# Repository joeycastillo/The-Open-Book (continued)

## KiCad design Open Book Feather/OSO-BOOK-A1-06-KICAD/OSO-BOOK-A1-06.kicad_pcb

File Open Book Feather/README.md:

# Notes on the Open Book PCB files

The current working, tested revision is **Open Book A1 Rev 06** (**OSO-BOOK-A1-06**). For the sake of clarity, I've removed revisions 01 through 04; if you made one of these old boards, these notes remain.

## Open Book A1 Rev 01 Errata

I imagine you don't have this board; it was the first test, and was replaced with revision 2 almost immediately. It had a couple of big issues:

* The buttons on the shift register floated, because there were no pull-up resistors. This rendered the buttons unusable.
* The Neopixel, in addition to being in a really inconvenient place, was powered by VHI instead of the 3V regulator, which made it power up before everything else and shine bright blue until you took control of it. It also wouldn't turn off when the enable switch was thrown.

## Open Book A1 Rev 02 Errata

There are two errors on this revision's descriptive silkscreen: first, at the bottom, in the "Button Register" block, the shift register's pins are listed as:

    Pins: 
    BUTTON_LATCH: D48/PB31
    BUTTON_OUT:  D49/PB30
    BUTTON_CLOCK: D50/PB00

The correct mapping is:

    Pins: 
    BUTTON_LATCH: D50/PB00
    BUTTON_OUT:  D49/PB30
    BUTTON_CLOCK: D48/PB31

Second, the SAM D51 Microcontroller block erroneously lists the UART's SERCOM as SERCOM0. It is in fact SERCOM5.

## Open Book A1 Rev 03

Revision 3 was never fabricated; it simply fixed the first error above, but was otherwise identical to Revision 2. I wanted to correct the error in case anyone was building along at home, and bumped the revision to make it clear which version had the issue. It still has the incorrect SERCOM listed, though; that was not caught until later.

Note that the pin muxing changed after revision 3; if you have board revision A1-01, A1-02 or A1-03, you will need to set a flag when compiling your code. In the Arduino IDE, this setting is in `Tools -> Hardware Revision`. In CircuitPython, you can just use the digital pin numbers as labeled on your silkscreen to access the correct pins.

## Open Book A1 Rev 04

This board has the final pinout (no need to set the Hardware Revision flag), and adds several features:

* Microphone shutdown pin
* USB voltage monitor (detect when plugged in to external power)
* Battery full indicator

This is the last revision with the SERCOM0/SERCOM5 silkscreen error.

## Open Book A1 Rev 05

This is identical to Rev 04, but fixes the silkscreen error in the SAM D51 block. It also adds a RC filter to the USB cable shield (recommendation from the SAM D51 data sheet), and tweaks the through-hole button footprints for a slightly better fit.

This version works quite well. If you have this version, there is no need to get the A1-06 version.

## Open Book A1 Rev 06

This is the final version of the A1-type hardware. It adds pull-up resistors for the Babel Flash chip and MicroSD card, and bias resistors for the audio output on the headphone jack.

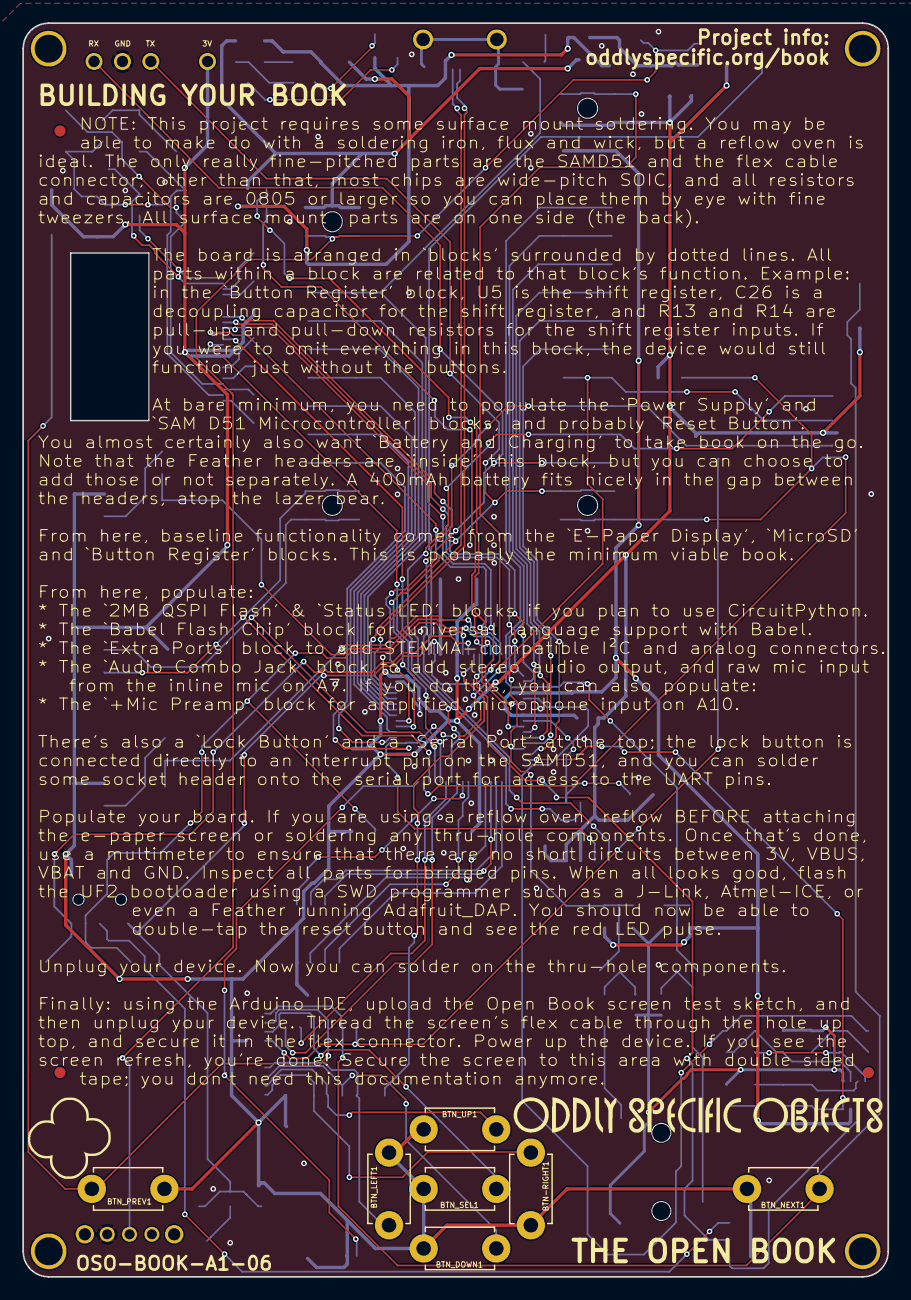
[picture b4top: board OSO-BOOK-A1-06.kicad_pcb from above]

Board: 2 copper layers, 77.5 x 112.3 mm, 136 parts (0 on the bottom side), 100 nets.

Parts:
BTN-RIGHT1: SWITCH_PUSHBUTTONEVQ-PE; TACT_PANA-EVQ
BTN_DOWN1: SWITCH_PUSHBUTTONEVQ-PE; TACT_PANA-EVQ
BTN_LEFT1: SWITCH_PUSHBUTTONEVQ-PE; TACT_PANA-EVQ
BTN_LOCK1: SPST_TACTILE_SWITCHRA; TL3330AF130QG
BTN_NEXT1: SWITCH_PUSHBUTTONEVQ-PE; TACT_PANA-EVQ
BTN_PREV1: SWITCH_PUSHBUTTONEVQ-PE; TACT_PANA-EVQ
BTN_RESET1: SPST_TACTILE_SWITCHRA; TL3330AF130QG
BTN_SEL1: SWITCH_PUSHBUTTONEVQ-PE; TACT_PANA-EVQ
BTN_UP1: SWITCH_PUSHBUTTONEVQ-PE; TACT_PANA-EVQ
C1, C2, C4, C11: 10µF; 0805-NO
C3, C9, C12, C14, C15, C16, C17, C29: 1uF; 0805-NO
C5, C7, C25: 10uF; 0805_10MGAP
C6, C8, C10, C26, C28: 1uF; 0805_10MGAP
C13: 0.1uF; 0805_10MGAP
C18, C19, C20, C21, C22, C23: 1uF/25V; 0805-NO
C24: 4.7uF/25V; 0805-NO
C27, C35: 10uF; 0805-NO
C30, C31: 100uF; C1210
C32: 0.1µF; 0805-NO
C33: 0.01uF; 0805-NO
C34: 100pF; 0805-NO
C36: 4.5nF; 0805-NO
CHG1: AMBER; CHIP-LED0805
D1: MBR120; SOD-123
D2, D3, D4: MBR0530; SOD-123
D5, D6: 3.6V; SOD-123
DNP_NEXT_ALT1: SPST_TACTILE_SWITCHRA; TL3330AF130QG
DNP_PREV_ALT1: SPST_TACTILE_SWITCHRA; TL3330AF130QG
FB1, FB2: Ferrite; 0805
FID1, FID2, FID3, FID4, FID5, FID6: FIDUCIAL_1MM
FUL1: GREEN; CHIP-LED0805
GOLD_ORB_SM1: OSHWLOGOLOGO5MM; OSHW_5MM
J1: SJ-43514-SMT; CUI_SJ-43514-SMT
J2: 10118193-0001LF; FCI_10118193-0001LF
JP1: PINHD-1X3; 1X03
JP2: PINHD-1X1; 1X01
L1: 10uH; MICROBUILDER_INDUCTOR_4X4MM_NR401_BIGPADS
LED1: RED; CHIP-LED0805
MICROSD1: MICROSD
MS1: FEATHERWING_SMTDUAL; FEATHERWING_SMT2
NEOPIX1: WS2812B_4020
PORT_A8, PORT_A9: JST PH 3; JSTPH3
PORT_I2C1: JST PH 4; JSTPH4
Q1: DMG341; SOT23-R
Q2: IRLML0100; SOT23-3
R1, R3: 10K; 0805-NO
R2, R11, R26: 100K; 0805-NO
R4, R5, R10, R21, R22, R25: 1K; 0805-NO
R6, R13, R14: 100K; EXBV8V
R7, R8, R28, R29: 10K; 0805_10MGAP
R9: 100; 0805_10MGAP
R12: 0.47ohm; 0805_10MGAP
R15, R16: 1K; _0805MP
R17, R18, R19, R20: 100; 0805-NO
R23, R24, R27: 1M; 0805-NO
R30, R31, R32, R33: 10K; _0805MP
SJ1: SOLDERJUMPER_FIVEWAY
SW1: SPDT_SWITCH; A10767
TP1, TP2, TP6, TP7, TP8: TESTPOINTROUND2MMNO; TESTPOINT_ROUND_2MM_NO
U1: AP2112-3.3; SOT23-5
U2: MCP73831T-2ACI/OT; SOT23-5
U3: ATSAMD51J64-TQFP(10X10); TQFP64-10X10
U4: GD25Q16C; SOIC8_150MIL
U5: 74AC165D; SO16
U6: GD25Q16C; MICROBUILDER_SOIC8_150MIL
U7: MAX4468EKAT; SOT65P280X145-8N
U$1, U$4, U$5, U$7: MOUNTINGHOLE2.5; MOUNTINGHOLE_2.5_PLATED
U$2: WAVESHARE_4_2_INCH_EINK_DISPLAY; EINK_DISPLAY_4_2IN
U$45: OSO_WORDMARK_125X1300MIL_1000DPI
U$47: OSO_BEAR_525X750MIL_1000DPI
U$48: OSO-LOGO-250MIL
U$49: OSO_WORDMARK_THREELINE_450MIL_1000DPI
X1: JSTPH; JSTPH2
X2: 2x5 0.05" SWD; 2X05_1.27MM_BOX_POSTS

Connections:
+3V3: BTN-RIGHT1.P$2, BTN_DOWN1.P$2, BTN_LEFT1.P$2, BTN_NEXT1.P$2, BTN_PREV1.P$2, BTN_SEL1.P$2, BTN_UP1.P$2, C2.1, C3.1, C5.1, C6.1, C9.1, C10.1, C14.1, C17.2, C25.1, C26.1, C27.1, C28.1, C29.1, DNP_NEXT_ALT1.P$2, DNP_PREV_ALT1.P$2, FB1.1, JP2.1, L1.P$1, MICROSD1.4, MS1.2, MS1.2', NEOPIX1.2, PORT_A8.2, PORT_A9.2, PORT_I2C1.2, R7.1, R8.1, R11.1, R13.5, R28.1, R29.1, SJ1.3, TP2.P$1, U1.5, U3.21, U3.34, U3.48, U3.56, U4.8, U5.16, U6.3, U6.7, U6.8, U$2.15, U$2.16, X2.1
/OSO-BOOK-A1-06_1/A2: MS1.7, MS1.7', U3.11
/OSO-BOOK-A1-06_1/A3: MS1.8, MS1.8', U3.12
/OSO-BOOK-A1-06_1/A4: MS1.9, MS1.9', U3.13
/OSO-BOOK-A1-06_1/A5: MS1.10, MS1.10', U3.15
/OSO-BOOK-A1-06_1/A6_BATMON: R6.1, R6.2, U3.62
/OSO-BOOK-A1-06_1/A11_BUSMON: R6.3, R6.4, U3.61
/OSO-BOOK-A1-06_1/D5: MS1.19, MS1.19', U3.35
/OSO-BOOK-A1-06_1/D6: MS1.20, MS1.20', U3.37
/OSO-BOOK-A1-06_1/D9: MS1.21, MS1.21', U3.38
/OSO-BOOK-A1-06_1/D10: MS1.22, MS1.22', U3.41
/OSO-BOOK-A1-06_1/D11: MS1.23, MS1.23', U3.42
/OSO-BOOK-A1-06_1/D12: MS1.24, MS1.24', U3.43
/OSO-BOOK-A1-06_1/SWCLK: R7.2, TP6.P$1, U3.57, X2.4
/OSO-BOOK-A1-06_1/SWDIO: TP7.P$1, U3.58, X2.2
/OSO-BOOK-A1-06_1/USB_N: J2.2, U3.45
/OSO-BOOK-A1-06_1/USB_P: J2.3, U3.46
/OSO-BOOK-A1-06_1/~RESET: C13.2, MS1.1, MS1.1', R8.2, R9.2, TP8.P$1, U3.52, X2.10
/OSO-BOOK-A1-06_2/BUTTON0: BTN_LEFT1.P$1, R14.1, U5.11
/OSO-BOOK-A1-06_2/BUTTON1: BTN_DOWN1.P$1, R14.2, U5.12
/OSO-BOOK-A1-06_2/BUTTON2: BTN_UP1.P$1, R14.3, U5.13
/OSO-BOOK-A1-06_2/BUTTON3: BTN-RIGHT1.P$1, R14.4, U5.14
/OSO-BOOK-A1-06_2/BUTTON4: BTN_SEL1.P$1, R13.3, U5.3
/OSO-BOOK-A1-06_2/BUTTON5: BTN_PREV1.P$1, DNP_PREV_ALT1.P$1, R13.2, U5.4
/OSO-BOOK-A1-06_2/BUTTON6: BTN_NEXT1.P$1, DNP_NEXT_ALT1.P$1, R13.1, U5.5
/OSO-BOOK-A1-06_2/BUTTON7: MICROSD1.CD2, R13.4, U5.6
/OSO-BOOK-A1-06_2/GDR: Q2.1, U$2.2
/OSO-BOOK-A1-06_2/PREVGH: C23.1, D4.C, U$2.21
/OSO-BOOK-A1-06_2/PREVGL: C22.1, D3.A, U$2.23
/OSO-BOOK-A1-06_2/RESE: Q2.2, R12.1, U$2.3
/OSO-BOOK-A1-06_2/VCOM: C21.2, U$2.24
/OSO-BOOK-A1-06_2/VDD: C18.2, U$2.18
/OSO-BOOK-A1-06_2/VGH: C16.2, U$2.5
/OSO-BOOK-A1-06_2/VGL: C15.2, U$2.4
/OSO-BOOK-A1-06_2/VSH: C19.2, U$2.20
/OSO-BOOK-A1-06_2/VSL: C20.2, U$2.22
/OSO-BOOK-A1-06_3/MICAMP_SHDN: SJ1.2, U7.6
/OSO-BOOK-A1-06_3/MIC_BIAS_PWR: R22.2, R24.2, U7.4
A0: MS1.5, MS1.5', R17.2, R30.2, R31.1, U3.3
A1: MS1.6, MS1.6', R19.2, R32.2, R33.1, U3.14
A7_MIC: C33.1, J1.1, R21.1, U3.5
A10_MICAMP: C34.1, R26.2, U3.16, U7.8
AGND: C32.2, C35.2, FB2.1, J1.4, R18.1, R20.1, R23.1, R31.2, R33.2, U7.1
AVCC: C11.1, C12.1, FB1.2, MS1.3, MS1.3', R30.1, R32.1, U3.4, U3.8, U7.7
BUTTONLOCK: BTN_LOCK1.P$1, U3.51
BUTTON_CLK: U3.27, U5.2
BUTTON_LATCH: U3.25, U5.1
BUTTON_OUT: U3.59, U5.9
D2_A8: D5.C, R15.2, U3.64
D3_A9: D6.C, R16.2, U3.63
D4_SDCS: MICROSD1.2, MS1.16, MS1.16', R28.2, U3.31
D8_NEOPIX: NEOPIX1.1, U3.32
D13: MS1.25, MS1.25', R10.1, U3.44
EINK_BUSY: U3.2, U$2.9
EINK_CS: U3.10, U$2.12
EINK_DC: U3.6, U$2.11
EINK_MOSI: U3.28, U$2.14
EINK_RST: U3.1, U$2.10
EINK_SCK: U3.26, U$2.13
EN: MS1.27, MS1.27', R1.1, SW1.P$2, U1.3
GND: BTN_LOCK1.P$2, BTN_RESET1.P$1, C1.2, C2.2, C3.2, C4.2, C5.2, C6.2, C7.2, C8.2, C9.2, C10.2, C11.2, C12.2, C13.1, C14.2, C15.1, C16.1, C17.1, C18.1, C19.1, C20.1, C21.1, C22.2, C23.2, C25.2, C26.2, C27.2, C28.2, C29.2, C36.2, D2.C, D5.A, D6.A, FB2.2, FUL1.C, J2.5, JP1.2, LED1.C, MICROSD1.6, MICROSD1.MT1, MICROSD1.MT2, MS1.4, MS1.4', NEOPIX1.4, PORT_A8.1, PORT_A9.1, PORT_I2C1.1, R2.2, R3.2, R6.5, R6.7, R12.2, R13.6, R13.7, R13.8, R14.5, R14.6, R14.7, R14.8, R27.2, SJ1.4, SW1.P$3, TP1.P$1, U1.2, U2.2, U3.7, U3.22, U3.33, U3.47, U3.54, U4.4, U5.8, U5.10, U5.15, U6.4, U$2.8, U$2.17, X1.1, X2.3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
MISO: MICROSD1.7, MS1.13, MS1.13', U3.49, U6.2
MOSI: MICROSD1.3, MS1.12, MS1.12', U3.50, U6.5
unnamed: BTN_RESET1.P$2, R9.1
unnamed: C7.1, C8.1, U3.53
unnamed: C24.1, D4.A, L1.P$2, Q2.3
unnamed: C24.2, D2.A, D3.C
unnamed: C30.1, R17.1, R18.2
unnamed: C30.2, J1.3
unnamed: C31.1, R19.1, R20.2
unnamed: C31.2, J1.2
unnamed: C32.1, R21.2, R22.1
unnamed: C33.2, R23.2, R24.1, U7.2
unnamed: C34.2, R25.1, R26.1, U7.3
unnamed: C35.1, R25.2
unnamed: C36.1, J2.S1, J2.S2, J2.S3, J2.S4, J2.S5, J2.S6, R27.1
unnamed: CHG1.C, R4.1
unnamed: FUL1.A, R5.1
unnamed: LED1.A, R10.2
unnamed: PORT_A8.3, R15.1
unnamed: PORT_A9.3, R16.1
unnamed: R3.1, U2.5
unnamed: R4.2, R5.2, U2.1
PB31_SWO_MICSHDN: SJ1.1, U3.60
QSPI_CS: R11.2, U3.24, U4.1
QSPI_DATA[0]: U3.17, U4.5
QSPI_DATA[1]: U3.18, U4.2
QSPI_DATA[2]: U3.19, U4.3
QSPI_DATA[3]: U3.20, U4.7
QSPI_SCK: U3.23, U4.6
RX: JP1.3, MS1.14, MS1.14', U3.40
SCK: MICROSD1.5, MS1.11, MS1.11', U3.36, U6.6
SCL: MS1.18, MS1.18', PORT_I2C1.4, U3.30
SDA: MS1.17, MS1.17', PORT_I2C1.3, U3.29
SWO: SJ1.5, X2.6
TX: JP1.1, MS1.15, MS1.15', U3.39
UNIFONT_CS: R29.2, U3.9, U6.1
V+: C1.1, D1.C, Q1.2, R1.2, U1.1
VBAT: C4.1, MS1.28, MS1.28', Q1.3, R6.8, U2.3, X1.2
VBUS: CHG1.A, D1.A, J2.1, MS1.26, MS1.26', Q1.1, R2.1, R6.6, U2.4

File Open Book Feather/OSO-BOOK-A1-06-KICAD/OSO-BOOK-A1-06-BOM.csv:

Reference, Quantity, Value, Footprint, Datasheet
BTN-RIGHT1 BTN_DOWN1 BTN_LEFT1 BTN_NEXT1 BTN_PREV1 BTN_SEL1 BTN_UP1 ,7,"SWITCH_PUSHBUTTONEVQ-PE","OSO-BOOK-A1-06:TACT_PANA-EVQ",""
BTN_LOCK1 BTN_RESET1 DNP_NEXT_ALT1 DNP_PREV_ALT1 ,4,"SPST_TACTILE_SWITCHRA","OSO-BOOK-A1-06:TL3330AF130QG",""
C1 C11 C2 C4 ,4,"10µF","OSO-BOOK-A1-06:0805-NO",""
C13 ,1,"0.1uF","OSO-BOOK-A1-06:0805_10MGAP",""
C18 C19 C20 C21 C22 C23 ,6,"1uF/25V","OSO-BOOK-A1-06:0805-NO",""
C24 ,1,"4.7uF/25V","OSO-BOOK-A1-06:0805-NO",""
C27 C35 ,2,"10uF","OSO-BOOK-A1-06:0805-NO",""
C12 C14 C15 C16 C17 C29 C3 C9 ,8,"1uF","OSO-BOOK-A1-06:0805-NO",""
C30 C31 ,2,"100uF","OSO-BOOK-A1-06:C1210",""
C32 ,1,"0.1µF","OSO-BOOK-A1-06:0805-NO",""
C33 ,1,"0.01uF","OSO-BOOK-A1-06:0805-NO",""
C34 ,1,"100pF","OSO-BOOK-A1-06:0805-NO",""
C36 ,1,"4.5nF","OSO-BOOK-A1-06:0805-NO",""
C25 C5 C7 ,3,"10uF","OSO-BOOK-A1-06:0805_10MGAP",""
C10 C26 C28 C6 C8 ,5,"1uF","OSO-BOOK-A1-06:0805_10MGAP",""
CHG1 ,1,"AMBER","OSO-BOOK-A1-06:CHIP-LED0805",""
D1 ,1,"MBR120","OSO-BOOK-A1-06:SOD-123",""
D2 D3 D4 ,3,"MBR0530","OSO-BOOK-A1-06:SOD-123",""
D5 D6 ,2,"3.6V","OSO-BOOK-A1-06:SOD-123",""
FB1 FB2 ,2,"Ferrite","OSO-BOOK-A1-06:0805",""
FID1 FID2 FID3 FID4 FID5 FID6 ,6,"FIDUCIAL_1MM","OSO-BOOK-A1-06:FIDUCIAL_1MM",""
FUL1 ,1,"GREEN","OSO-BOOK-A1-06:CHIP-LED0805",""
GOLD_ORB_SM1 ,1,"OSHWLOGOLOGO5MM","OSO-BOOK-A1-06:OSHW_5MM",""
J1 ,1,"SJ-43514-SMT","OSO-BOOK-A1-06:CUI_SJ-43514-SMT",""
J2 ,1,"10118193-0001LF","OSO-BOOK-A1-06:FCI_10118193-0001LF",""
JP1 ,1,"PINHD-1X3","OSO-BOOK-A1-06:1X03",""
JP2 ,1,"PINHD-1X1","OSO-BOOK-A1-06:1X01",""
L1 ,1,"10uH","OSO-BOOK-A1-06:MICROBUILDER_INDUCTOR_4X4MM_NR401_BIGPADS",""
LED1 ,1,"RED","OSO-BOOK-A1-06:CHIP-LED0805",""
MICROSD1 ,1,"MICROSD","OSO-BOOK-A1-06:MICROSD",""
MS1 ,1,"FEATHERWING_SMTDUAL","OSO-BOOK-A1-06:FEATHERWING_SMT2",""
NEOPIX1 ,1,"WS2812B_4020","OSO-BOOK-A1-06:WS2812B_4020",""
PORT_A8 PORT_A9 ,2,"JST PH 3","OSO-BOOK-A1-06:JSTPH3",""
PORT_I2C1 ,1,"JST PH 4","OSO-BOOK-A1-06:JSTPH4",""
Q1 ,1,"DMG341","OSO-BOOK-A1-06:SOT23-R",""
Q2 ,1,"IRLML0100","OSO-BOOK-A1-06:SOT23-3",""
R1 R3 ,2,"10K","OSO-BOOK-A1-06:0805-NO",""
R12 ,1,"0.47ohm","OSO-BOOK-A1-06:0805_10MGAP",""
R15 R16 ,2,"1K","OSO-BOOK-A1-06:_0805MP",""
R11 R2 R26 ,3,"100K","OSO-BOOK-A1-06:0805-NO",""
R17 R18 R19 R20 ,4,"100","OSO-BOOK-A1-06:0805-NO",""
R23 R24 R27 ,3,"1M","OSO-BOOK-A1-06:0805-NO",""
R30 R31 R32 R33 ,4,"10K","OSO-BOOK-A1-06:_0805MP",""
R10 R21 R22 R25 R4 R5 ,6,"1K","OSO-BOOK-A1-06:0805-NO",""
R13 R14 R6 ,3,"100K","OSO-BOOK-A1-06:EXBV8V",""
R28 R29 R7 R8 ,4,"10K","OSO-BOOK-A1-06:0805_10MGAP",""
R9 ,1,"100","OSO-BOOK-A1-06:0805_10MGAP",""
SJ1 ,1,"SOLDERJUMPER_FIVEWAY","OSO-BOOK-A1-06:SOLDERJUMPER_FIVEWAY",""
SW1 ,1,"SPDT_SWITCH","OSO-BOOK-A1-06:A10767",""
TP1 TP2 TP6 TP7 TP8 ,5,"TESTPOINTROUND2MMNO","OSO-BOOK-A1-06:TESTPOINT_ROUND_2MM_NO",""
U$1 U$4 U$5 U$7 ,4,"MOUNTINGHOLE2.5","OSO-BOOK-A1-06:MOUNTINGHOLE_2.5_PLATED",""
U$2 ,1,"WAVESHARE_4_2_INCH_EINK_DISPLAY","OSO-BOOK-A1-06:EINK_DISPLAY_4_2IN",""
U1 ,1,"AP2112-3.3","OSO-BOOK-A1-06:SOT23-5",""
U2 ,1,"MCP73831T-2ACI/OT","OSO-BOOK-A1-06:SOT23-5",""
U3 ,1,"ATSAMD51J64-TQFP(10X10)","OSO-BOOK-A1-06:TQFP64-10X10",""
U4 ,1,"GD25Q16C","OSO-BOOK-A1-06:SOIC8_150MIL",""
U5 ,1,"74AC165D","OSO-BOOK-A1-06:SO16",""
U6 ,1,"GD25Q16C","OSO-BOOK-A1-06:MICROBUILDER_SOIC8_150MIL",""
U7 ,1,"MAX4468EKAT","OSO-BOOK-A1-06:SOT65P280X145-8N",""
X1 ,1,"JSTPH","OSO-BOOK-A1-06:JSTPH2",""
X2 ,1,"2x5 0.05" SWD","OSO-BOOK-A1-06:2X05_1.27MM_BOX_POSTS",""

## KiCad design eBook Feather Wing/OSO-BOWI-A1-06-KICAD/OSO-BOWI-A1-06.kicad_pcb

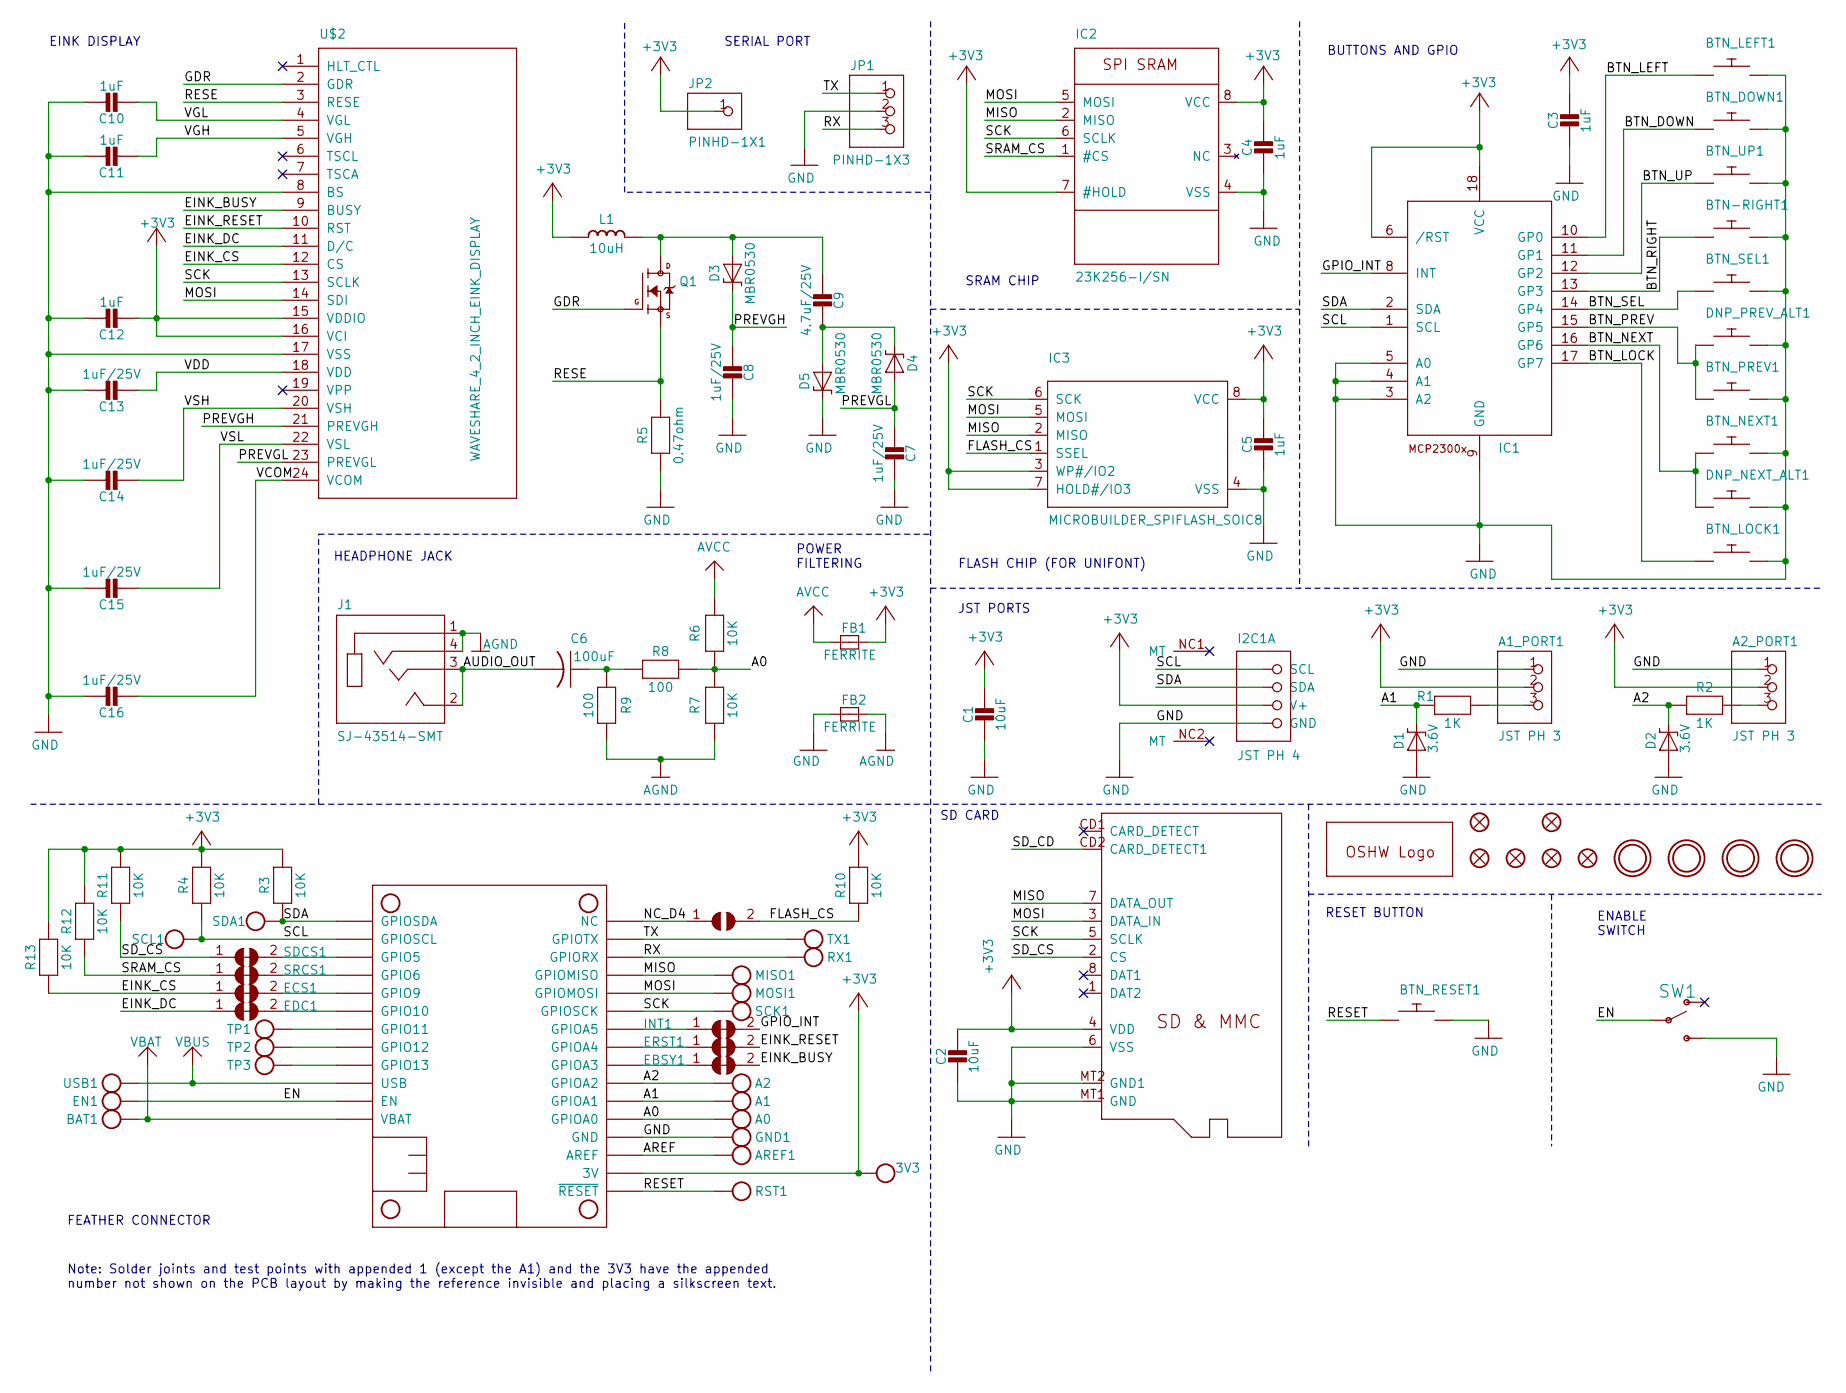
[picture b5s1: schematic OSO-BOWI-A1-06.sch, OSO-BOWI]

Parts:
3V3: MICROBUILDER_TESTPOINT1.5X2.0MM_NOCREAM; MICROBUILDER_PAD-1.5X2.0
A0, A1, A2: MICROBUILDER_TESTPOINT1.5X2.0MM_NOCREAM; MICROBUILDER_PAD-1.5X2.0
A1_PORT1, A2_PORT1: JST PH 3; JSTPH3
AREF1: MICROBUILDER_TESTPOINT1.5X2.0MM_NOCREAM; MICROBUILDER_PAD-1.5X2.0
BAT1: MICROBUILDER_TESTPOINT1.5X2.0MM_NOCREAM; MICROBUILDER_PAD-1.5X2.0
BCS1: SOLDERJUMPER_OPEN
BTN-RIGHT1: SWITCH_PUSHBUTTONEVQ-PE; TACT_PANA-EVQ
BTN_DOWN1: SWITCH_PUSHBUTTONEVQ-PE; TACT_PANA-EVQ
BTN_LEFT1: SWITCH_PUSHBUTTONEVQ-PE; TACT_PANA-EVQ
BTN_LOCK1: SWITCH_PUSHBUTTONC&K_KSS; BTN_CK_KSS
BTN_NEXT1: SWITCH_PUSHBUTTONEVQ-PE; TACT_PANA-EVQ
BTN_PREV1: SWITCH_PUSHBUTTONEVQ-PE; TACT_PANA-EVQ
BTN_RESET1: SWITCH_PUSHBUTTONC&K_KSS; BTN_CK_KSS
BTN_SEL1: SWITCH_PUSHBUTTONEVQ-PE; TACT_PANA-EVQ
BTN_UP1: SWITCH_PUSHBUTTONEVQ-PE; TACT_PANA-EVQ
C1: 10uF; 0805-NO
C2: 10uF; 0805_10MGAP
C3, C4, C5: 1uF; 0805_10MGAP
C6: 100uF; C1210
C7, C8, C13, C14, C15, C16: 1uF/25V; 0805-NO
C9: 4.7uF/25V; 0805-NO
C10, C11, C12: 1uF; 0805-NO
D1, D2: 3.6V; SOD-123
D3, D4, D5: MBR0530; SOD-123
DNP_NEXT_ALT1: SPST_TACTILE_SWITCHRA; TL3330AF130QG
DNP_PREV_ALT1: SPST_TACTILE_SWITCHRA; TL3330AF130QG
EBSY1: MICROBUILDER_SOLDERJUMPER_CLOSED; MICROBUILDER_SOLDERJUMPER_CLOSEDWIRE
ECS1: MICROBUILDER_SOLDERJUMPER_CLOSED; MICROBUILDER_SOLDERJUMPER_CLOSEDWIRE
EDC1: MICROBUILDER_SOLDERJUMPER_CLOSED; MICROBUILDER_SOLDERJUMPER_CLOSEDWIRE
EN1: MICROBUILDER_TESTPOINT1.5X2.0MM_NOCREAM; MICROBUILDER_PAD-1.5X2.0
ERST1: MICROBUILDER_SOLDERJUMPER_CLOSED; MICROBUILDER_SOLDERJUMPER_CLOSEDWIRE
FB1, FB2: FERRITE; 0805
FID1, FID2, FID3, FID4, FID5, FID6: FIDUCIAL_1MM
GND1: MICROBUILDER_TESTPOINT1.5X2.0MM_NOCREAM; MICROBUILDER_PAD-1.5X2.0
GOLD_ORB_SM1: OSHWLOGOLOGO5MM; OSHW_5MM
I2C1: JST PH 4; JSTPH4
IC1: MCP23008_SO; SO18W
IC2: 23K256-I/SN; SOIC8_150MIL
IC3: MICROBUILDER_SPIFLASH_SOIC8; MICROBUILDER_SOIC8_150MIL
INT1: MICROBUILDER_SOLDERJUMPER_CLOSED; MICROBUILDER_SOLDERJUMPER_CLOSEDWIRE
J1: SJ-43514-SMT; CUI_SJ-43514-SMT
JP1: PINHD-1X3; 1X03
JP2: PINHD-1X1; 1X01
L1: 10uH; MICROBUILDER_INDUCTOR_4X4MM_NR401_BIGPADS
MICROSD1: MICROSD
MISO1: MICROBUILDER_TESTPOINT1.5X2.0MM_NOCREAM; MICROBUILDER_PAD-1.5X2.0
MOSI1: MICROBUILDER_TESTPOINT1.5X2.0MM_NOCREAM; MICROBUILDER_PAD-1.5X2.0
MS1: MICROBUILDER_FEATHERWING_SMTDUAL_NOLINES; MICROBUILDER_FEATHERWING_SMT2_NOLINES
Q1: IRLML0100; SOT23-3
R1, R2: 1K; _0805MP
R3, R4, R6, R7, R10, R11, R12, R13: 10K; _0805MP
R5: 0.47ohm; 0805_10MGAP
R8, R9: 100; _0805MP
RST1: MICROBUILDER_TESTPOINT1.5X2.0MM_NOCREAM; MICROBUILDER_PAD-1.5X2.0
RX1: MICROBUILDER_TESTPOINT1.5X2.0MM_NOCREAM; MICROBUILDER_PAD-1.5X2.0
SCK1: MICROBUILDER_TESTPOINT1.5X2.0MM_NOCREAM; MICROBUILDER_PAD-1.5X2.0
SCL1: MICROBUILDER_TESTPOINT1.5X2.0MM_NOCREAM; MICROBUILDER_PAD-1.5X2.0
SDA1: MICROBUILDER_TESTPOINT1.5X2.0MM_NOCREAM; MICROBUILDER_PAD-1.5X2.0
SDCS1: MICROBUILDER_SOLDERJUMPER_CLOSED; MICROBUILDER_SOLDERJUMPER_CLOSEDWIRE
SRCS1: MICROBUILDER_SOLDERJUMPER_CLOSED; MICROBUILDER_SOLDERJUMPER_CLOSEDWIRE
SW1: SPDT_SWITCH; A10767
TP1, TP2, TP3: MICROBUILDER_TESTPOINT1.5X2.0MM_NOCREAM; MICROBUILDER_PAD-1.5X2.0
TX1: MICROBUILDER_TESTPOINT1.5X2.0MM_NOCREAM; MICROBUILDER_PAD-1.5X2.0
U$1, U$4, U$5, U$7: MOUNTINGHOLE2.5; MOUNTINGHOLE_2.5_PLATED
U$2: WAVESHARE_4_2_INCH_EINK_DISPLAY; EINK_DISPLAY_4_2IN
USB1: MICROBUILDER_TESTPOINT1.5X2.0MM_NOCREAM; MICROBUILDER_PAD-1.5X2.0

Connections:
+3V3: 3V3.P$1, A1_PORT1.2, A2_PORT1.2, C1.1, C2.1, C3.1, C4.1, C5.1, C12.2, FB1.2, I2C1.2 (V+), IC1.6 (/RST), IC1.18 (VCC), IC2.7 (#HOLD), IC2.8 (VCC), IC3.3 (WP#/IO2), IC3.7 (HOLD#/IO3), IC3.8 (VCC), JP2.1, L1.P$1 (1), MICROSD1.4 (VDD), MS1.2 (3V), MS1.2' (3V), R3.1, R4.1, R10.1, R11.1, R12.1, R13.1, U$2.15 (VDDIO), U$2.16 (VCI)
/A0: A0.P$1, MS1.5 (GPIOA0), MS1.5' (GPIOA0), R6.2, R7.1, R8.1
/A1: A1.P$1, D1.C, MS1.6 (GPIOA1), MS1.6' (GPIOA1), R1.2
/A2: A2.P$1, D2.C, MS1.7 (GPIOA2), MS1.7' (GPIOA2), R2.2
/AREF: AREF1.P$1, MS1.3 (AREF), MS1.3' (AREF)
/AUDIO_OUT: C6.2, J1.2 (TIP), J1.3 (RING1)
/BTN_DOWN: BTN_DOWN1.P$1, IC1.11 (GP1)
/BTN_LEFT: BTN_LEFT1.P$1, IC1.10 (GP0)
/BTN_LOCK: BTN_LOCK1.P$1, IC1.17 (GP7)
/BTN_NEXT: BTN_NEXT1.P$1, DNP_NEXT_ALT1.P$1, IC1.16 (GP6)
/BTN_PREV: BTN_PREV1.P$1, DNP_PREV_ALT1.P$1, IC1.15 (GP5)
/BTN_RIGHT: BTN-RIGHT1.P$1, IC1.13 (GP3)
/BTN_SEL: BTN_SEL1.P$1, IC1.14 (GP4)
/BTN_UP: BTN_UP1.P$1, IC1.12 (GP2)
/EINK_BUSY: EBSY1.2, U$2.9 (BUSY)
/EINK_CS: ECS1.1, R13.2, U$2.12 (CS)
/EINK_DC: EDC1.1, U$2.11 (D/C)
/EINK_RESET: ERST1.2, U$2.10 (RST)
/EN: EN1.P$1, MS1.27 (EN), MS1.27' (EN), SW1.P$2
/FLASH_CS: BCS1.2, IC3.1 (SSEL), R10.2
/GDR: Q1.1 (G), U$2.2 (GDR)
/GPIO_INT: IC1.8 (INT), INT1.2
/MISO: IC2.2 (MISO), IC3.2 (MISO), MICROSD1.7 (DATA_OUT), MISO1.P$1, MS1.13 (GPIOMISO), MS1.13' (GPIOMISO)
/MOSI: IC2.5 (MOSI), IC3.5 (MOSI), MICROSD1.3 (DATA_IN), MOSI1.P$1, MS1.12 (GPIOMOSI), MS1.12' (GPIOMOSI), U$2.14 (SDI)
/NC_D4: BCS1.1, MS1.16 (NC), MS1.16' (NC)
/PREVGH: C8.1, D3.C, U$2.21 (PREVGH)
/PREVGL: C7.1, D4.A, U$2.23 (PREVGL)
/RESE: Q1.2 (S), R5.1, U$2.3 (RESE)
/RESET: BTN_RESET1.P$1, MS1.1 (~RESET), MS1.1' (~RESET), RST1.P$1
/RX: JP1.3, MS1.14 (GPIORX), MS1.14' (GPIORX), RX1.P$1
/SCK: IC2.6 (SCLK), IC3.6 (SCK), MICROSD1.5 (SCLK), MS1.11 (GPIOSCK), MS1.11' (GPIOSCK), SCK1.P$1, U$2.13 (SCLK)
/SCL: I2C1.4 (SCL), IC1.1 (SCL), MS1.18 (GPIOSCL), MS1.18' (GPIOSCL), R4.2, SCL1.P$1
/SDA: I2C1.3 (SDA), IC1.2 (SDA), MS1.17 (GPIOSDA), MS1.17' (GPIOSDA), R3.2, SDA1.P$1
/SD_CS: MICROSD1.2 (CS), R11.2, SDCS1.1
/SRAM_CS: IC2.1 (#CS), R12.2, SRCS1.1
/TX: JP1.1, MS1.15 (GPIOTX), MS1.15' (GPIOTX), TX1.P$1
/VCOM: C16.2, U$2.24 (VCOM)
/VDD: C13.2, U$2.18 (VDD)
/VGH: C11.2, U$2.5 (VGH)
/VGL: C10.2, U$2.4 (VGL)
/VSH: C14.2, U$2.20 (VSH)
/VSL: C15.2, U$2.22 (VSL)
AGND: FB2.2, J1.1 (SLEEVE), J1.4 (RING2), R7.2, R9.1
AVCC: FB1.1, R6.1
GND: A1_PORT1.1, A2_PORT1.1, BTN-RIGHT1.P$2, BTN_DOWN1.P$2, BTN_LEFT1.P$2, BTN_LOCK1.P$2, BTN_NEXT1.P$2, BTN_PREV1.P$2, BTN_RESET1.P$2, BTN_SEL1.P$2, BTN_UP1.P$2, C1.2, C2.2, C3.2, C4.2, C5.2, C7.2, C8.2, C10.1, C11.1, C12.1, C13.1, C14.1, C15.1, C16.1, D1.A, D2.A, D5.C, DNP_NEXT_ALT1.P$2, DNP_PREV_ALT1.P$2, FB2.1, GND1.P$1, I2C1.1 (GND), IC1.3 (A2), IC1.4 (A1), IC1.5 (A0), IC1.9 (GND), IC2.4 (VSS), IC3.4 (VSS), JP1.2, MICROSD1.6 (VSS), MICROSD1.MT1 (GND), MICROSD1.MT2 (GND1), MS1.4 (GND), MS1.4' (GND), R5.2, SW1.P$3 (S), U$2.8 (BS), U$2.17 (VSS)
unnamed: A1_PORT1.3, R1.1
unnamed: A2_PORT1.3, R2.1
unnamed: C6.1, R8.2, R9.2
unnamed: C9.1, D3.A, L1.P$2 (2), Q1.3 (D)
unnamed: C9.2, D4.C, D5.A
unnamed: EBSY1.1, MS1.8 (GPIOA3), MS1.8' (GPIOA3)
unnamed: ECS1.2, MS1.21 (GPIO9), MS1.21' (GPIO9)
unnamed: EDC1.2, MS1.22 (GPIO10), MS1.22' (GPIO10)
unnamed: ERST1.1, MS1.9 (GPIOA4), MS1.9' (GPIOA4)
unnamed: INT1.1, MS1.10 (GPIOA5), MS1.10' (GPIOA5)
unnamed: MS1.19 (GPIO5), MS1.19' (GPIO5), SDCS1.2
unnamed: MS1.20 (GPIO6), MS1.20' (GPIO6), SRCS1.2
unnamed: MS1.23 (GPIO11), MS1.23' (GPIO11), TP1.P$1
unnamed: MS1.24 (GPIO12), MS1.24' (GPIO12), TP2.P$1
unnamed: MS1.25 (GPIO13), MS1.25' (GPIO13), TP3.P$1
VBAT: BAT1.P$1, MS1.28 (VBAT), MS1.28' (VBAT)
VBUS: MS1.26 (USB), MS1.26' (USB), USB1.P$1

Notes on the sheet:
FEATHER CONNECTOR
SD CARD
EINK DISPLAY
HEADPHONE JACK
RESET BUTTON
ENABLE SWITCH
POWER FILTERING
BUTTONS AND GPIO
JST PORTS
SRAM CHIP
FLASH CHIP (FOR UNIFONT)
SERIAL PORT
Note: Solder joints and test points with appended 1 (except the A1) and the 3V3 have the appended number not shown on the PCB layout by making the reference invisible and placing a silkscreen text.

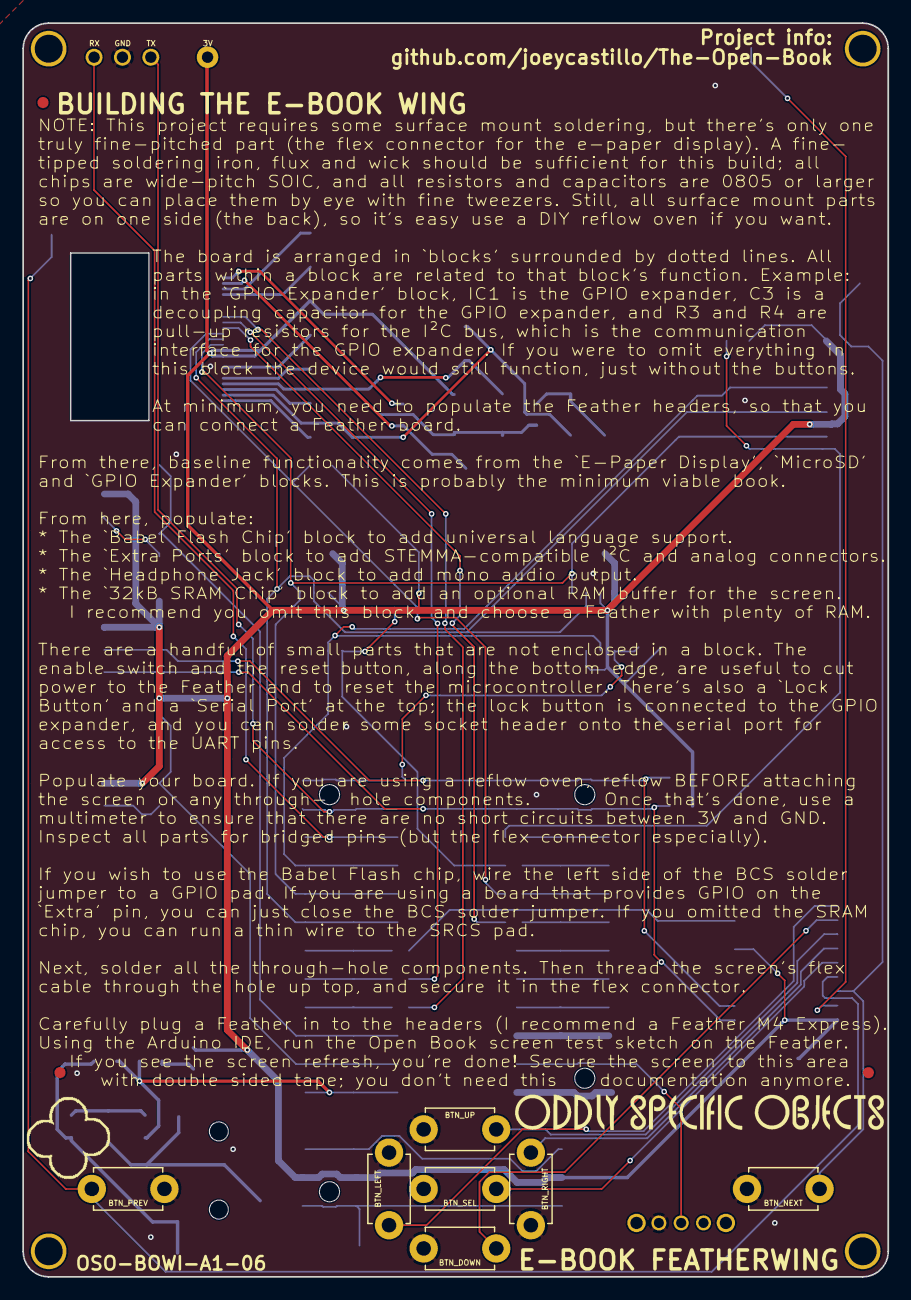
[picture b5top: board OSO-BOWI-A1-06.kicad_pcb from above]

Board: 2 copper layers, 77.5 x 112.3 mm, 105 parts (0 on the bottom side), 62 nets.

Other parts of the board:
U$11, U$13: OSO_WORDMARK_125X1300MIL_1000DPI
U$15: OSO_BEAR_250X360MIL_1000DPI
U$44: OSO_GRAPHIC

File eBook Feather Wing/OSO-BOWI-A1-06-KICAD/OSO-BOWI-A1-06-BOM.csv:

Reference, Quantity, Value, Footprint, Datasheet
A1_PORT1 A2_PORT1 ,2,"JST PH 3","OSO-BOWI-A1-06:JSTPH3",""
BCS1 ,1,"SOLDERJUMPER_OPEN","OSO-BOWI-A1-06:SOLDERJUMPER_OPEN",""
BTN-RIGHT1 BTN_DOWN1 BTN_LEFT1 BTN_NEXT1 BTN_PREV1 BTN_SEL1 BTN_UP1 ,7,"SWITCH_PUSHBUTTONEVQ-PE","OSO-BOWI-A1-06:TACT_PANA-EVQ",""
BTN_LOCK1 BTN_RESET1 ,2,"SWITCH_PUSHBUTTONC&K_KSS","OSO-BOWI-A1-06:BTN_CK_KSS",""
C1 ,1,"10uF","OSO-BOWI-A1-06:0805-NO",""
C10 C11 C12 ,3,"1uF","OSO-BOWI-A1-06:0805-NO",""
C13 C14 C15 C16 C7 C8 ,6,"1uF/25V","OSO-BOWI-A1-06:0805-NO",""
C2 ,1,"10uF","OSO-BOWI-A1-06:0805_10MGAP",""
C3 C4 C5 ,3,"1uF","OSO-BOWI-A1-06:0805_10MGAP",""
C6 ,1,"100uF","OSO-BOWI-A1-06:C1210",""
C9 ,1,"4.7uF/25V","OSO-BOWI-A1-06:0805-NO",""
D1 D2 ,2,"3.6V","OSO-BOWI-A1-06:SOD-123",""
D3 D4 D5 ,3,"MBR0530","OSO-BOWI-A1-06:SOD-123",""
DNP_NEXT_ALT1 DNP_PREV_ALT1 ,2,"SPST_TACTILE_SWITCHRA","OSO-BOWI-A1-06:TL3330AF130QG",""
FB1 FB2 ,2,"FERRITE","OSO-BOWI-A1-06:0805",""
FID1 FID2 FID3 FID4 FID5 FID6 ,6,"FIDUCIAL_1MM","OSO-BOWI-A1-06:FIDUCIAL_1MM",""
GOLD_ORB_SM1 ,1,"OSHWLOGOLOGO5MM","OSO-BOWI-A1-06:OSHW_5MM",""
I2C1 ,1,"JST PH 4","OSO-BOWI-A1-06:JSTPH4",""
IC1 ,1,"MCP23008_SO","OSO-BOWI-A1-06:SO18W",""
IC2 ,1,"23K256-I/SN","OSO-BOWI-A1-06:SOIC8_150MIL",""
IC3 ,1,"MICROBUILDER_SPIFLASH_SOIC8","OSO-BOWI-A1-06:MICROBUILDER_SOIC8_150MIL",""
J1 ,1,"SJ-43514-SMT","OSO-BOWI-A1-06:CUI_SJ-43514-SMT",""
JP1 ,1,"PINHD-1X3","OSO-BOWI-A1-06:1X03",""
JP2 ,1,"PINHD-1X1","OSO-BOWI-A1-06:1X01",""
L1 ,1,"10uH","OSO-BOWI-A1-06:MICROBUILDER_INDUCTOR_4X4MM_NR401_BIGPADS",""
MICROSD1 ,1,"MICROSD","OSO-BOWI-A1-06:MICROSD",""
MS1 ,1,"MICROBUILDER_FEATHERWING_SMTDUAL_NOLINES","OSO-BOWI-A1-06:MICROBUILDER_FEATHERWING_SMT2_NOLINES",""
Q1 ,1,"IRLML0100","OSO-BOWI-A1-06:SOT23-3",""
R1 R2 ,2,"1K","OSO-BOWI-A1-06:_0805MP",""
R5 ,1,"0.47ohm","OSO-BOWI-A1-06:0805_10MGAP",""
R10 R11 R12 R13 R3 R4 R6 R7 ,8,"10K","OSO-BOWI-A1-06:_0805MP",""
R8 R9 ,2,"100","OSO-BOWI-A1-06:_0805MP",""
EBSY1 ECS1 EDC1 ERST1 INT1 SDCS1 SRCS1 ,7,"MICROBUILDER_SOLDERJUMPER_CLOSED","OSO-BOWI-A1-06:MICROBUILDER_SOLDERJUMPER_CLOSEDWIRE",""
SW1 ,1,"SPDT_SWITCH","OSO-BOWI-A1-06:A10767",""
3V3 A0 A1 A2 AREF1 BAT1 EN1 GND1 MISO1 MOSI1 RST1 RX1 SCK1 SCL1 SDA1 TP1 TP2 TP3 TX1 USB1 ,20,"MICROBUILDER_TESTPOINT1.5X2.0MM_NOCREAM","OSO-BOWI-A1-06:MICROBUILDER_PAD-1.5X2.0",""
U$1 U$4 U$5 U$7 ,4,"MOUNTINGHOLE2.5","OSO-BOWI-A1-06:MOUNTINGHOLE_2.5_PLATED",""
U$2 ,1,"WAVESHARE_4_2_INCH_EINK_DISPLAY","OSO-BOWI-A1-06:EINK_DISPLAY_4_2IN",""

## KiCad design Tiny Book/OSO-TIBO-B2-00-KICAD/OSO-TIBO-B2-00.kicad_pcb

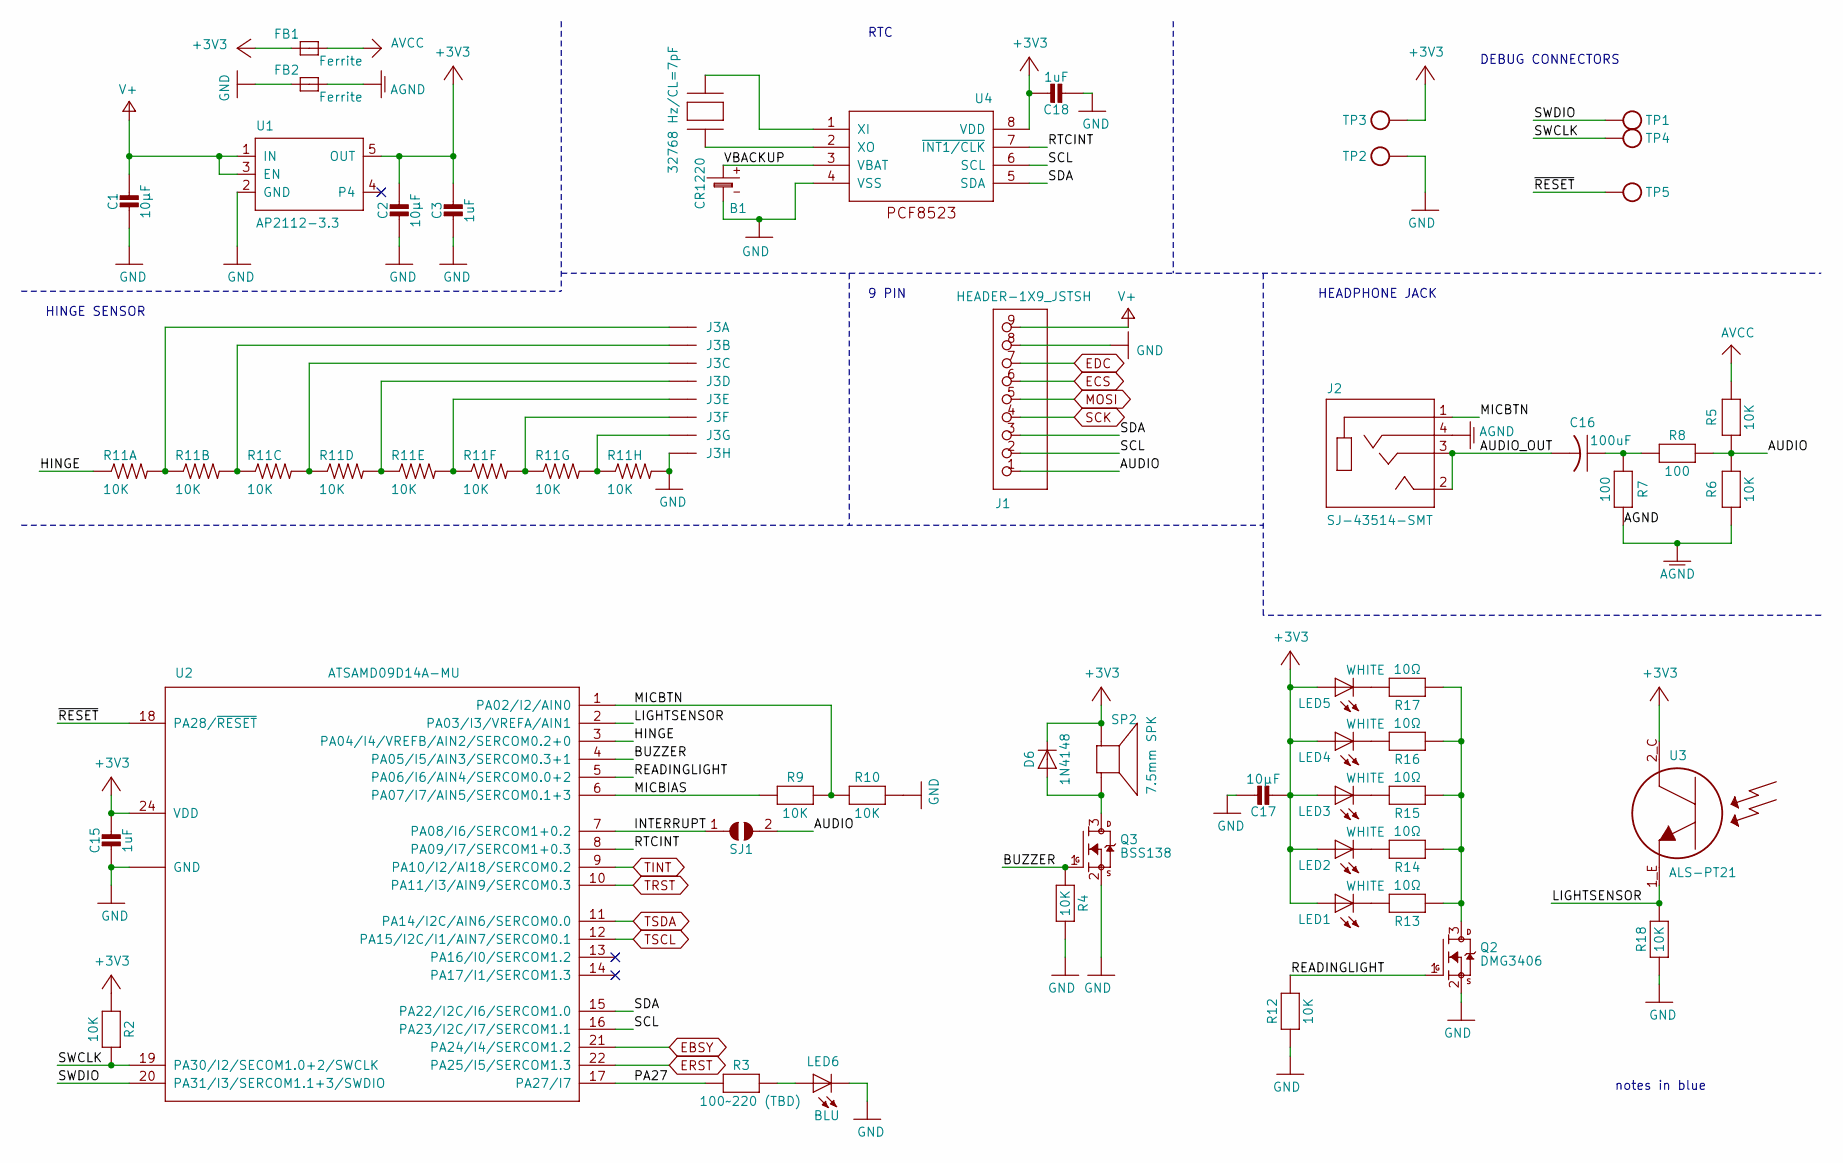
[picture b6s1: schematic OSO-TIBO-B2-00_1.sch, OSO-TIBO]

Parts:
B1: CR1220
C1, C2, C17: 10µF; 0805-NO
C3, C15, C18: 1uF; 0805-NO
C16: 100uF; C1210
D6: 1N4148; SOD-123
FB1, FB2: Ferrite; 0805
J1: HEADER-1X9_JSTSH; JST_SH9
J2: SJ-43514-SMT; CUI_SJ-43514-SMT
J3: 52746-8
LED: BLU; CHIPLED_0805
LED1, LED2, LED3, LED4, LED5: WHITE; CHIPLED_0805
Q2: DMG3406; SOT23-WIDE
Q3: BSS138; SOT23-WIDE
R2, R4, R9, R10, R12, R18: 10K; 0805-NO
R3: 100~~220 (TBD); 0805-NO
R5, R6: 10K; _0805MP
R7, R8: 100; _0805MP
R11: 10K; EXB2HV
R13, R14, R15, R16, R17: 10Ω; 0805-NO
SJ1: SOLDERJUMPERREFLOW_NOPASTE; SOLDERJUMPER_REFLOW_NOPASTE
SP2: 7.5mm SPK; BUZZER_SMT_5MM
TP1, TP2, TP3, TP4, TP5: TESTPOINTROUND2MMNO; TESTPOINT_ROUND_2MM_NO
U1: AP2112-3.3; SOT23-5
U2: ATSAMD09D14A-MU; QFN24_4MM
U3: ALS-PT21; ALS-PT26-21C
U4: PCF8523T; SOIC8_150MIL
X1: 32768 Hz/CL=7pF; XTAL3215

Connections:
+3V3: C2.1, C3.1, C15.1, C17.2, C18.1, D6.C, FB1.1, LED1.A, LED2.A, LED3.A, LED4.A, LED5.A, R2.1, SP2.-, TP3.P$1, U1.5 (OUT), U2.24 (VDD), U3.2_C (C), U4.8 (VDD); also elsewhere on the board
/OSO-TIBO-B2-00_1/AUDIO: J1.1, R5.2, R6.1, R8.1, SJ1.2
/OSO-TIBO-B2-00_1/AUDIO_OUT: C16.2, J2.2 (TIP), J2.3 (RING1)
/OSO-TIBO-B2-00_1/BUZZER: Q3.1 (G), R4.1, U2.4 (PA05/I5/AIN3/SERCOM0.3+1)
/OSO-TIBO-B2-00_1/HINGE: R11.1, U2.3 (PA04/I4/VREFB/AIN2/SERCOM0.2+0)
/OSO-TIBO-B2-00_1/INTERRUPT: SJ1.1, U2.7 (PA08/I6/SERCOM1+0.2)
/OSO-TIBO-B2-00_1/LIGHTSENSOR: R18.2, U2.2 (PA03/I3/VREFA/AIN1), U3.1_E (E)
/OSO-TIBO-B2-00_1/MICBIAS: R9.1, U2.6 (PA07/I7/AIN5/SERCOM0.1+3)
/OSO-TIBO-B2-00_1/MICBTN: J2.1 (SLEEVE), R9.2, R10.1, U2.1 (PA02/I2/AIN0)
/OSO-TIBO-B2-00_1/PA27: R3.1, U2.17 (PA27/I7)
/OSO-TIBO-B2-00_1/READINGLIGHT: Q2.1 (G), R12.2, U2.5 (PA06/I6/AIN4/SERCOM0.0+2)
/OSO-TIBO-B2-00_1/RTCINT: U2.8 (PA09/I7/SERCOM1+0.3), U4.7 (~INT1/CLK)
/OSO-TIBO-B2-00_1/SCL: J1.2, U2.16 (PA23/I2C/I7/SERCOM1.1), U4.6 (SCL)
/OSO-TIBO-B2-00_1/SDA: J1.3, U2.15 (PA22/I2C/I6/SERCOM1.0), U4.5 (SDA)
/OSO-TIBO-B2-00_1/SWCLK: R2.2, TP4.P$1, U2.19 (PA30/I2/SECOM1.0+2/SWCLK)
/OSO-TIBO-B2-00_1/SWDIO: TP1.P$1, U2.20 (PA31/I3/SERCOM1.1+3/SWDIO)
/OSO-TIBO-B2-00_1/VBACKUP: B1.+$1 (+), B1.+$2 (+), U4.3 (VBAT)
/OSO-TIBO-B2-00_1/~RESET: TP5.P$1, U2.18 (PA28/~RESET)
AGND: FB2.2, J2.4 (RING2), R6.2, R7.1
AVCC: FB1.2, R5.1
EBSY: U2.21 (PA24/I4/SERCOM1.2); also elsewhere on the board
ECS: J1.6; also elsewhere on the board
EDC: J1.7; also elsewhere on the board
ERST: U2.22 (PA25/I5/SERCOM1.3); also elsewhere on the board
GND: B1.-, C1.2, C2.2, C3.2, C15.2, C17.1, C18.2, FB2.1, J1.8, J3.8, Q2.2 (S), Q3.2 (S), R4.2, R10.2, R11.9 (2), R12.1, R18.1, TP2.P$1, U1.2 (GND), U2.23 (GND), U2.THERM (GND), U4.4 (VSS); also elsewhere on the board
MOSI: J1.5; also elsewhere on the board
unnamed: C16.1, R7.2, R8.2
unnamed: D6.A, Q3.3 (D), SP2.+
unnamed: J3.1, R11.2 (1), R11.16 (2)
unnamed: J3.2, R11.3 (1), R11.15 (2)
unnamed: J3.3, R11.4 (1), R11.14 (2)
unnamed: J3.4, R11.5 (1), R11.13 (2)
unnamed: J3.5, R11.6 (1), R11.12 (2)
unnamed: J3.6, R11.7 (1), R11.11 (2)
unnamed: J3.7, R11.8 (1), R11.10 (2)
unnamed: LED1.C, R13.2
unnamed: LED2.C, R14.2
unnamed: LED3.C, R15.2
unnamed: LED4.C, R16.2
unnamed: LED5.C, R17.2
unnamed 52: R3.2; also elsewhere on the board
unnamed: Q2.3 (D), R13.1, R14.1, R15.1, R16.1, R17.1
unnamed: U4.1 (XI), X1.P$2
unnamed: U4.2 (XO), X1.P$1
SCK: J1.4; also elsewhere on the board
TINT: U2.9 (PA10/I2/AI18/SERCOM0.2); also elsewhere on the board
TRST: U2.10 (PA11/I3/AIN9/SERCOM0.3); also elsewhere on the board
TSCL: U2.12 (PA15/I2C/I1/AIN7/SERCOM0.1); also elsewhere on the board
TSDA: U2.11 (PA14/I2C/AIN6/SERCOM0.0); also elsewhere on the board
V+: C1.1, J1.9, U1.1 (IN), U1.3 (EN)

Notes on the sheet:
DEBUG CONNECTORS
HINGE SENSOR
9 PIN
notes in blue
HEADPHONE JACK
RTC
